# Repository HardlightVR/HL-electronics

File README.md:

# Hardlight Electronics

Contains the PCBA designs used in the Hardlight suit, designed in Eagle™. 

### Organization
- **MKIIIA** contains older versions of the Hardlight electronics, used in the experimental run of 25. Also includes incomplete designs for a the HL Bluetooth module. 
- **MKIIIB** contains the final designs used in the 100 and 500 run HL releases, as well as the completed WiFi module. 

### Please note:
Hardlight VR was a complex project involving many dependencies. We have decided to open the code in the hopes that others may make use of the tools and plugins we built over the years. However, some software may not have been built or tested in some time, and may require changes to be used with the latest VR software and technology. 

### Contributing and Contact
We welcome any and all interest in derivative projects made from this software, edits to the software, and updates to the plugins and drivers! If you are interested in contributing to the public Hardlight repositories, please create an issue, or email hardlightvr@gmail.com.

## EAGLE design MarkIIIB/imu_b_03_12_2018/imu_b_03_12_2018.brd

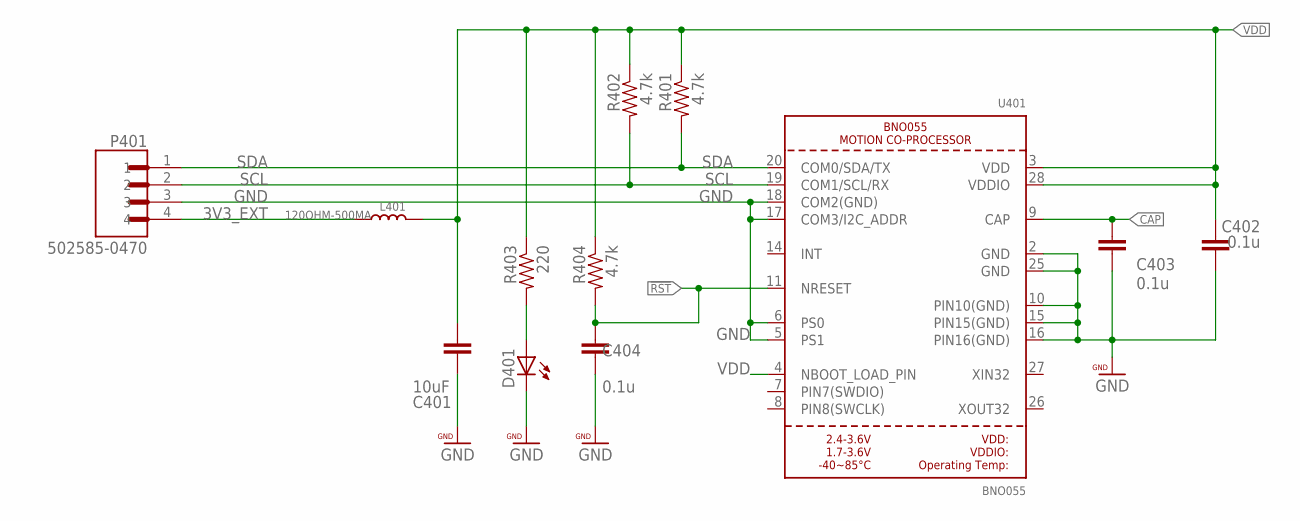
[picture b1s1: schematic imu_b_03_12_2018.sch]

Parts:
C401: 10uF; 0402-CAP
C402, C403, C404: 0.1u; 0402-CAP
D401: LEDCHIP-LED0603; CHIP-LED0603
L401: 120OHM-500MA; L0603
P401: 502585-0470; MOLEX_502585-0470
R401, R402, R404: 4.7k; EIA-0402
R403: 220; EIA-0402
U401: BNO055

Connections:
3V3_EXT: L401.2, P401.4
!RST: C404.1, R404.2, U401.11 (NRESET)
CAP: C403.1, U401.9 (CAP)
GND: C401.2, C402.2, C403.2, C404.2, D401.C, P401.3, U401.2 (GND), U401.5 (PS1), U401.6 (PS0), U401.10 (PIN10(GND)), U401.15 (PIN15(GND)), U401.16 (PIN16(GND)), U401.17 (COM3/I2C_ADDR), U401.18 (COM2(GND)), U401.25 (GND)
unnamed: D401.A, R403.2
SCL: P401.2, R402.2, U401.19 (COM1/SCL/RX)
SDA: P401.1, R401.2, U401.20 (COM0/SDA/TX)
VDD: C401.1, C402.1, L401.1, R401.1, R402.1, R403.1, R404.1, U401.3 (VDD), U401.4 (NBOOT_LOAD_PIN), U401.28 (VDDIO)

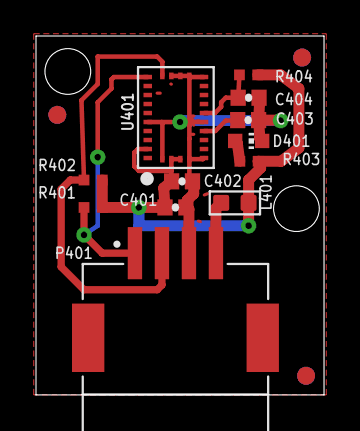
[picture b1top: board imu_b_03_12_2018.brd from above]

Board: 2 copper layers, 16.0 x 19.9 mm, 15 parts (0 on the bottom side), 8 nets.

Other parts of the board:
$$U$2: CIRCLE-1MM-2R
U$1, U$3: CIRCLE-1MM-2R

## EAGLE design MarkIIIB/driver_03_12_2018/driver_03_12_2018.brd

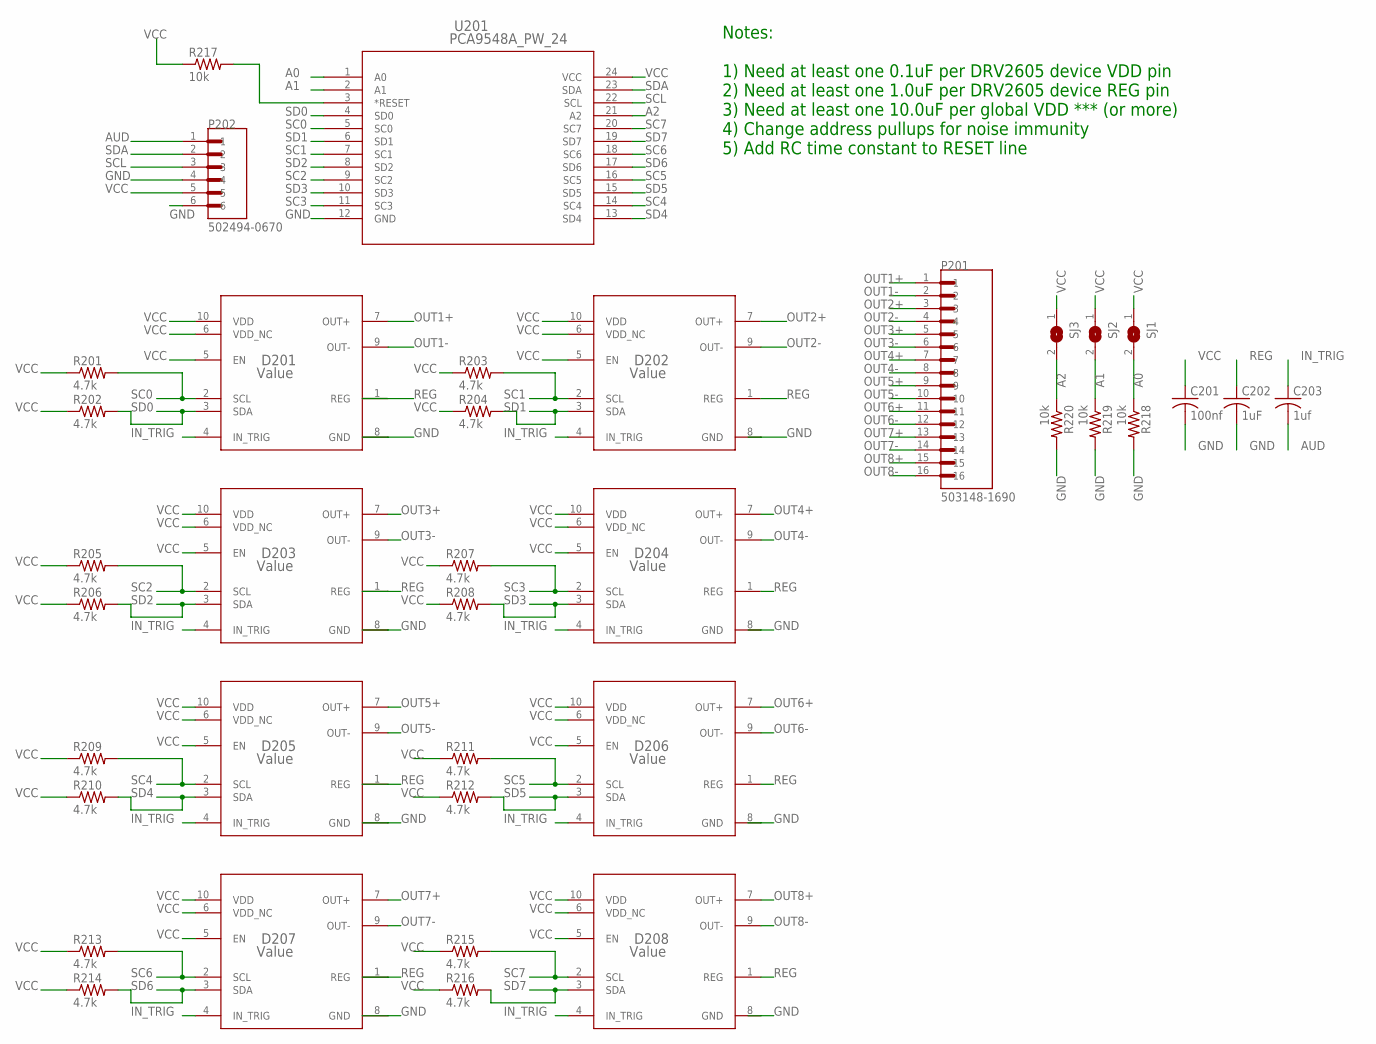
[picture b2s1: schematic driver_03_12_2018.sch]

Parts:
C201: 100nf; C0603
C202: 1uF; C0603
C203: 1uf; C0603
D201, D202, D203, D204, D205, D206, D207, D208: Value; DGS0010A
P201: 503148-1690; MOLEX_503148-1690
P202: 502494-0670; MOLEX_502494-0670
R201, R202, R203, R204, R205, R206, R207, R208, R209, R210, R211, R212, R213, R214, R215, R216: 4.7k; EIA-0402
R217: 10k; R0402
R218, R219, R220: 10k; EIA-0402
SJ1, SJ2, SJ3: SJ
U201: PCA9548A_PW_24; PW24

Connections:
A0: R218.1, SJ1.2, U201.1 (A0)
A1: R219.1, SJ2.2, U201.2 (A1)
A2: R220.1, SJ3.2, U201.21 (A2)
AUD: C203.2, P202.1
GND: C201.2, C202.2, D201.8 (GND), D202.8 (GND), D203.8 (GND), D204.8 (GND), D205.8 (GND), D206.8 (GND), D207.8 (GND), D208.8 (GND), P202.4, P202.6, R218.2, R219.2, R220.2, U201.12 (GND)
IN_TRIG: C203.1, D201.4 (IN_TRIG), D202.4 (IN_TRIG), D203.4 (IN_TRIG), D204.4 (IN_TRIG), D205.4 (IN_TRIG), D206.4 (IN_TRIG), D207.4 (IN_TRIG), D208.4 (IN_TRIG)
OUT1+: D201.7 (OUT+), P201.1
OUT1-: D201.9 (OUT-), P201.2
OUT2+: D202.7 (OUT+), P201.3
OUT2-: D202.9 (OUT-), P201.4
OUT3+: D203.7 (OUT+), P201.5
OUT3-: D203.9 (OUT-), P201.6
OUT4+: D204.7 (OUT+), P201.7
OUT4-: D204.9 (OUT-), P201.8
OUT5+: D205.7 (OUT+), P201.9
OUT5-: D205.9 (OUT-), P201.10
OUT6+: D206.7 (OUT+), P201.11
OUT6-: D206.9 (OUT-), P201.12
OUT7+: D207.7 (OUT+), P201.13
OUT7-: D207.9 (OUT-), P201.14
OUT8+: D208.7 (OUT+), P201.15
OUT8-: D208.9 (OUT-), P201.16
REG: C202.1, D201.1 (REG), D202.1 (REG), D203.1 (REG), D204.1 (REG), D205.1 (REG), D206.1 (REG), D207.1 (REG), D208.1 (REG)
RESET: R217.2, U201.3 (*RESET)
SC0: D201.2 (SCL), R201.2, U201.5 (SC0)
SC1: D202.2 (SCL), R203.2, U201.7 (SC1)
SC2: D203.2 (SCL), R205.2, U201.9 (SC2)
SC3: D204.2 (SCL), R207.2, U201.11 (SC3)
SC4: D205.2 (SCL), R209.2, U201.14 (SC4)
SC5: D206.2 (SCL), R211.2, U201.16 (SC5)
SC6: D207.2 (SCL), R213.2, U201.18 (SC6)
SC7: D208.2 (SCL), R215.2, U201.20 (SC7)
SCL: P202.3, U201.22 (SCL)
SD0: D201.3 (SDA), R202.2, U201.4 (SD0)
SD1: D202.3 (SDA), R204.2, U201.6 (SD1)
SD2: D203.3 (SDA), R206.2, U201.8 (SD2)
SD3: D204.3 (SDA), R208.2, U201.10 (SD3)
SD4: D205.3 (SDA), R210.2, U201.13 (SD4)
SD5: D206.3 (SDA), R212.2, U201.15 (SD5)
SD6: D207.3 (SDA), R214.2, U201.17 (SD6)
SD7: D208.3 (SDA), R216.2, U201.19 (SD7)
SDA: P202.2, U201.23 (SDA)
VCC: C201.1, D201.5 (EN), D201.6 (VDD_NC), D201.10 (VDD), D202.5 (EN), D202.6 (VDD_NC), D202.10 (VDD), D203.5 (EN), D203.6 (VDD_NC), D203.10 (VDD), D204.5 (EN), D204.6 (VDD_NC), D204.10 (VDD), D205.5 (EN), D205.6 (VDD_NC), D205.10 (VDD), D206.5 (EN), D206.6 (VDD_NC), D206.10 (VDD), D207.5 (EN), D207.6 (VDD_NC), D207.10 (VDD), D208.5 (EN), D208.6 (VDD_NC), D208.10 (VDD), P202.5, R201.1, R202.1, R203.1, R204.1, R205.1, R206.1, R207.1, R208.1, R209.1, R210.1, R211.1, R212.1, R213.1, R214.1, R215.1, R216.1, R217.1, SJ1.1, SJ2.1, SJ3.1, U201.24 (VCC)

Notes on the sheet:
Notes: 1) Need at least one 0.1uF per DRV2605 device VDD pin 2) Need at least one 1.0uF per DRV2605 device REG pin 3) Need at least one 10.0uF per global VDD *** (or more) 4) Change address pullups for noise immunity 5) Add RC time constant to RESET line

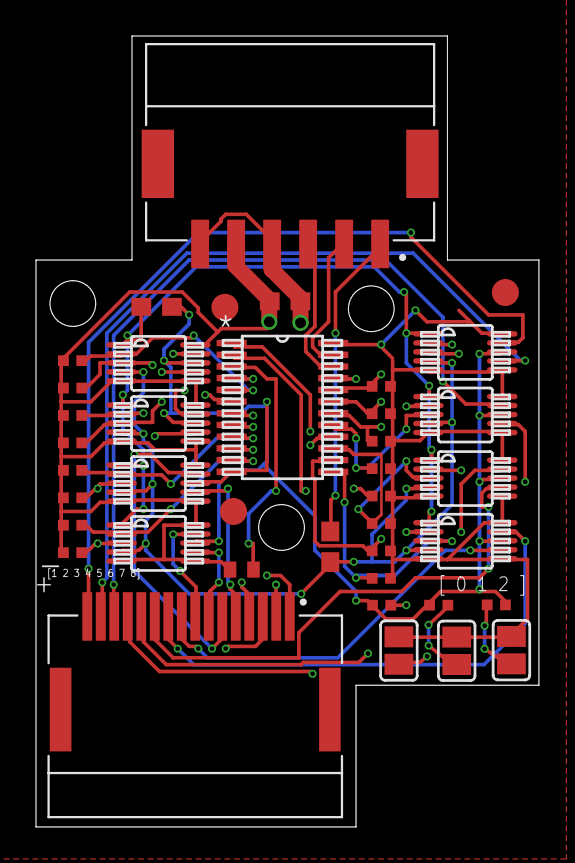
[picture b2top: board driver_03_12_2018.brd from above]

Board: 4 copper layers, 27.9 x 43.9 mm, 40 parts (0 on the bottom side), 43 nets.

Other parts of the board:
U$1, U$2, U$4: FIDUCIAL_G15

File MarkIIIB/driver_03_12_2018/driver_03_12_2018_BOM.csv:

Qty,Value,Device,Package,Parts,Description
3,,SJ,SJ,"SJ1, SJ2, SJ3",SMD solder JUMPER
1,100nf,C-USC0603,C0603,C201,"CAPACITOR, American symbol"
4,10k,R-US_R0402,R0402,"R219, R217, R218, R220","RESISTOR, American symbol"
1,1uF,C-USC0603,C0603,C202,"CAPACITOR, American symbol"
1,1uf,C-USC0603,C0603,C203,"CAPACITOR, American symbol"
16,4.7k,R-US_R0402,R0402,"R201, R202, R203, R204, R205, R206, R207, R208, R209, R210, R211, R212, R213, R214, R215, R216","RESISTOR, American symbol"
1,502494-0670,502494-0670,MOLEX_502494-0670,P202,"2.00mm Pitch CLIK-Mate Wire-to-Board PCB Receptacle, Single Row, Right Angle, 6 Circuits"
1,503148-1690,503148-1690,MOLEX_503148-1690,P201,"1.50mm Pitch CLIK-Mate Wire-to-Board PCB Receptacle, Dual Row, Right Angle, 16 Circuits"
1,PCA9548A_PW_24,PCA9548A_PW_24,PW24,U201,
8,Value,DRV2605LDGSR,DGS0010A,"D201, D202, D203, D204, D205, D206, D207, D208",

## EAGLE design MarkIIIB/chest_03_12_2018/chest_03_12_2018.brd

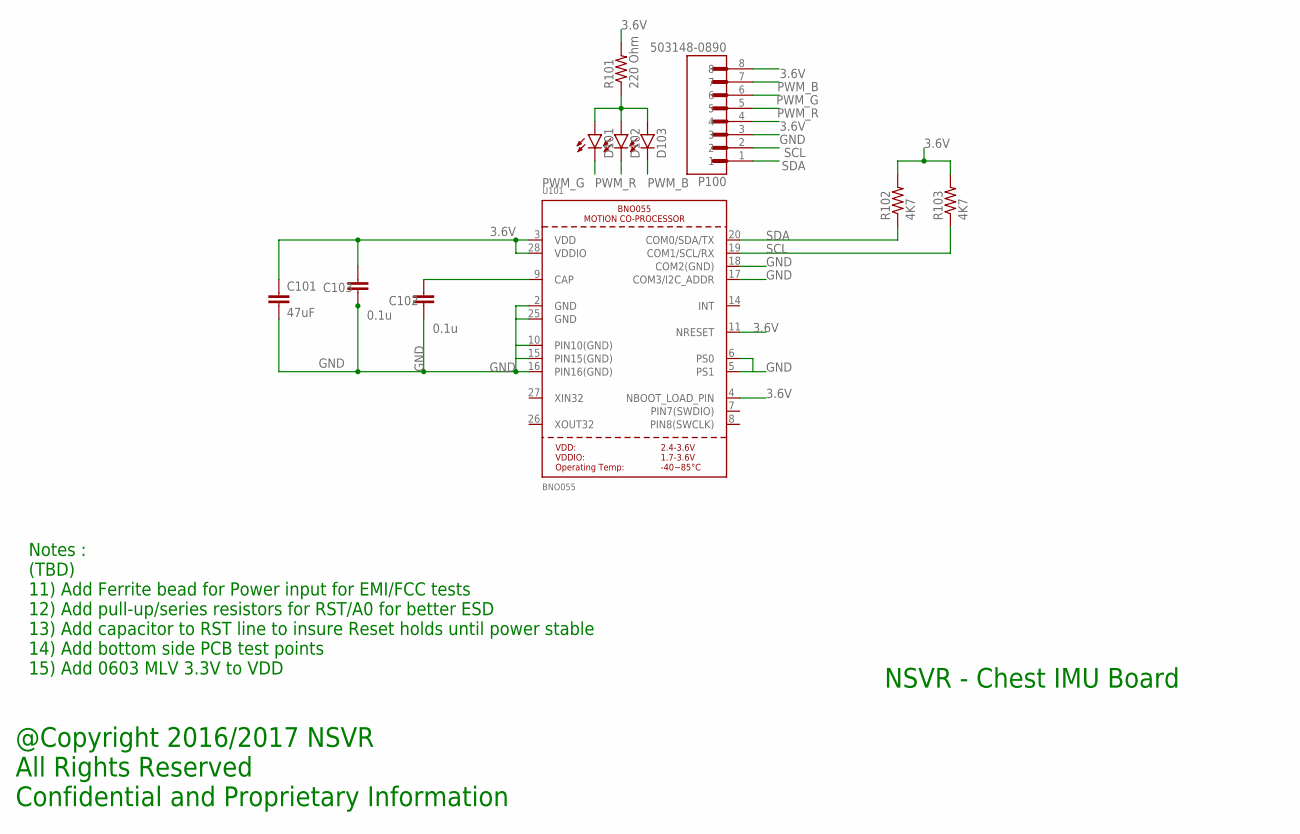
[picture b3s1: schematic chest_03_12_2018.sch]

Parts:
C101: 47uF; 1206
C102, C103: 0.1u; 0402-CAP
D101, D102, D103: LED0603; LED-0603
P100: 503148-0890; MOLEX_503148-0890
R101: 220 Ohm; EIA-0402
R102, R103: 4K7; EIA-0402
U101: BNO055

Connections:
3.6V: C101.1, C103.1, P100.4, P100.8, R101.2, R102.2, R103.2, U101.3 (VDD), U101.4 (NBOOT_LOAD_PIN), U101.11 (NRESET), U101.28 (VDDIO)
BYPASS: C102.1, U101.9 (CAP)
GND: C101.2, C102.2, C103.2, P100.3, U101.2 (GND), U101.5 (PS1), U101.6 (PS0), U101.10 (PIN10(GND)), U101.15 (PIN15(GND)), U101.16 (PIN16(GND)), U101.17 (COM3/I2C_ADDR), U101.18 (COM2(GND)), U101.25 (GND)
unnamed: D101.A, D102.A, D103.A, R101.1
PWM_B: D103.C, P100.7
PWM_G: D101.C, P100.6
PWM_R: D102.C, P100.5
SCL: P100.2, R103.1, U101.19 (COM1/SCL/RX)
SDA: P100.1, R102.1, U101.20 (COM0/SDA/TX)

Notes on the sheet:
NSVR - Chest IMU Board
@Copyright 2016/2017 NSVR All Rights Reserved Confidential and Proprietary Information
Notes : (TBD) 11) Add Ferrite bead for Power input for EMI/FCC tests 12) Add pull-up/series resistors for RST/A0 for better ESD 13) Add capacitor to RST line to insure Reset holds until power stable 14) Add bottom side PCB test points 15) Add 0603 MLV 3.3V to VDD

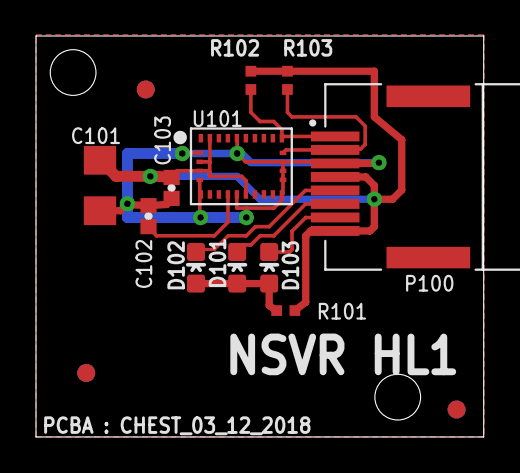
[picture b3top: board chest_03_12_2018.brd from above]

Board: 2 copper layers, 24.9 x 22.3 mm, 15 parts (1 on the bottom side), 9 nets.

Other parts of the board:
U$1, U$3, U$4: CIRCLE-1MM-3R
U$2: NSVR_LOGO

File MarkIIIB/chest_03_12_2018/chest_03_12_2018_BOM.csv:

"Qty";"Value";"Device";"Package";"Parts";"Description";"";
"3";"";"LED0603";"LED-0603";"D101, D102, D103";"LEDs";"";
"2";"0.1u";"C-USC0402";"C0402";"C102, C103";"CAPACITOR, American symbol";"";
"1";"220 Ohm";"R-US_R0402";"R0402";"R101";"RESISTOR, American symbol";"";
"1";"47uF";"CAP1206";"1206";"C101";"Capacitor";"";
"2";"4K7";"R-US_R0402";"R0402";"R102, R103";"RESISTOR, American symbol";"";
"1";"503148-0890";"503148-0890";"MOLEX_503148-0890";"P100";"1.5wb Dual r/a Embs Tape Pkg 8p";"";
"1";"BNO055";"BNO055";"BNO055";"U101";"BNO055 - Motion Co-Processor";"";

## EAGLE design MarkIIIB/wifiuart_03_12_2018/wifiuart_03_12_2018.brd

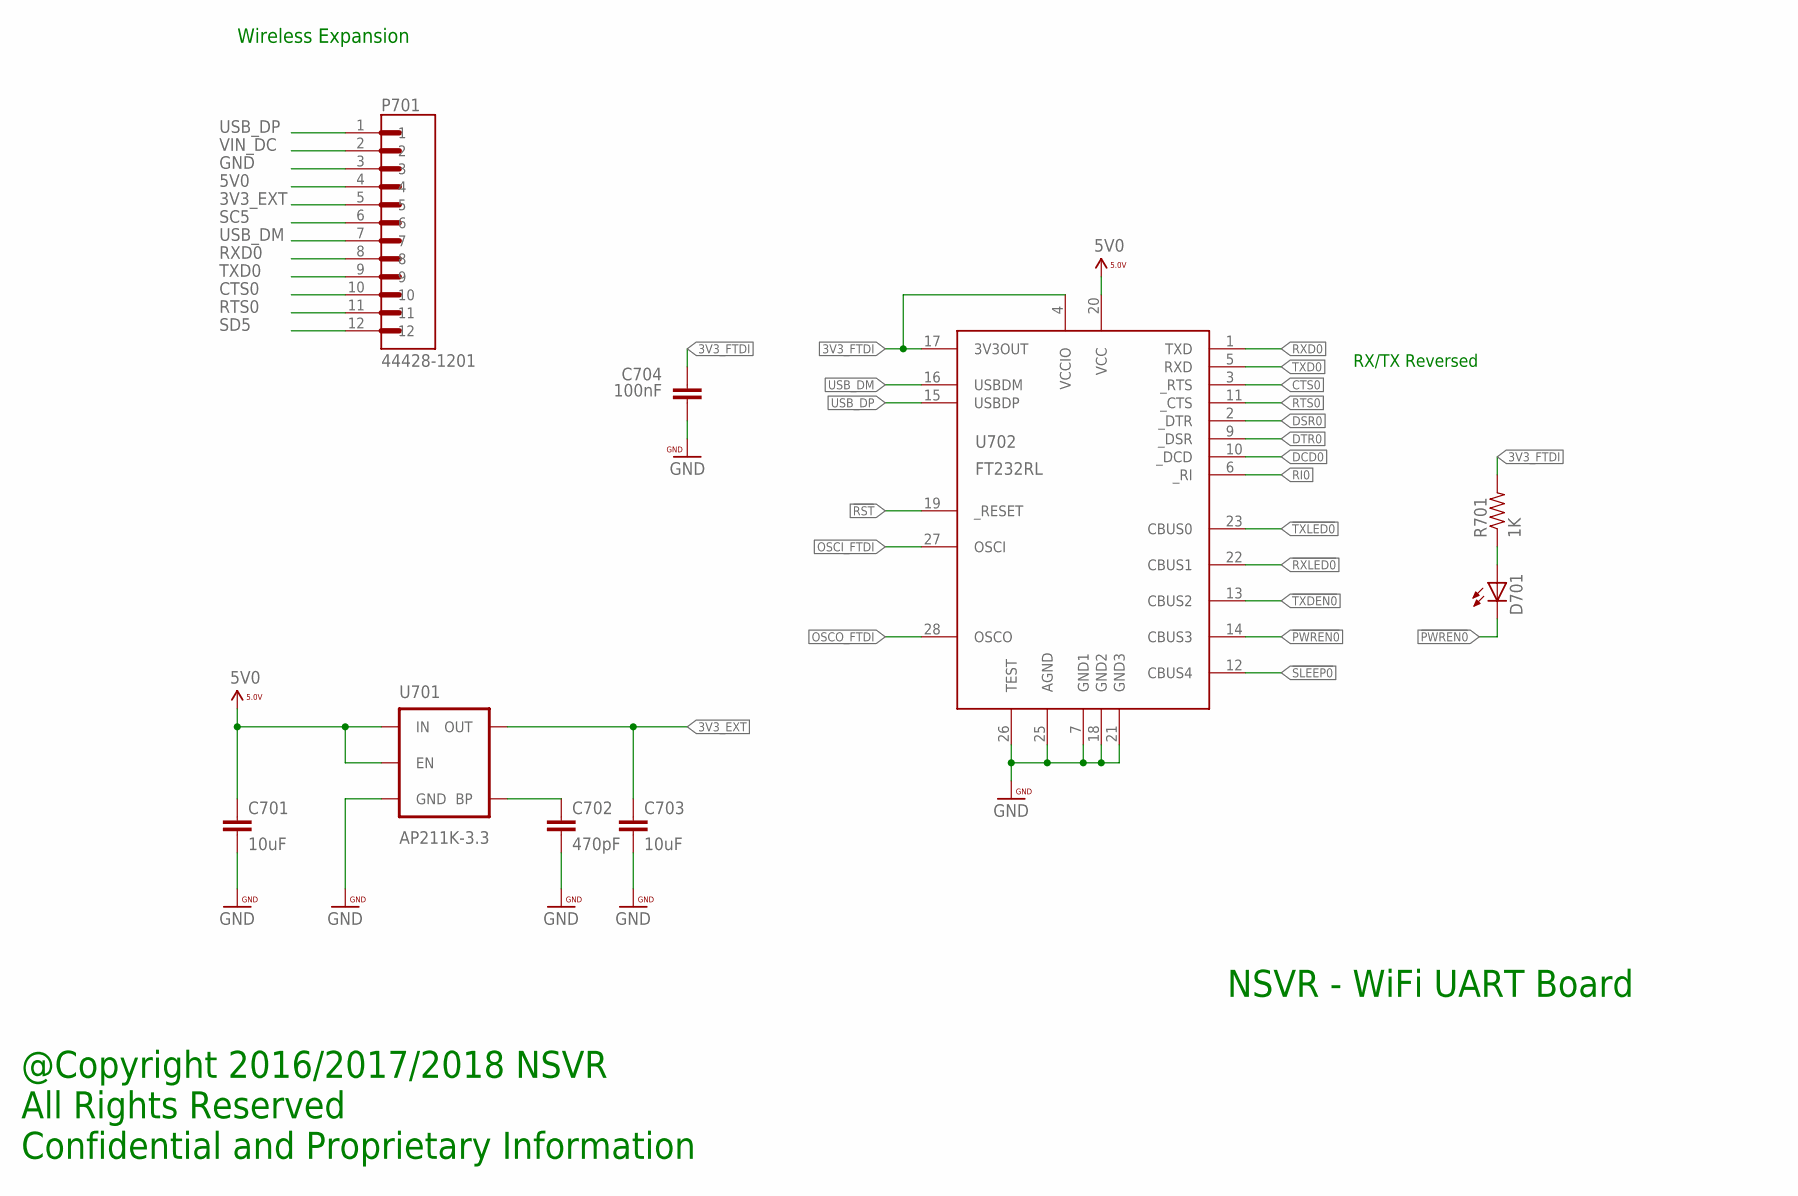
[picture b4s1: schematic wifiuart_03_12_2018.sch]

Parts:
C701, C703: 10uF; 0603-CAP
C702: 470pF; 0402-CAP
C704: 100nF; 0402-CAP
D701: LEDCHIP-LED0603; CHIP-LED0603
P701: 44428-1201; MOLEX_44428-1201
R701: 1K; EIA-0402
U701: AP211K-3.3; SOT23-5
U702: FT232RL; SSOP28DB

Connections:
3V3_EXT: C703.1, P701.5, U701.5 (OUT)
3V3_FTDI: C704.1, R701.2, U702.4 (VCCIO), U702.17 (3V3OUT)
5V0: C701.1, P701.4, U701.1 (IN), U701.3 (EN), U702.20 (VCC)
!PWREN0: D701.C, U702.14 (CBUS3)
!RST: U702.19 (_RESET)
!RXLED0: U702.22 (CBUS1)
!SLEEP0: U702.12 (CBUS4)
!TXDEN0: U702.13 (CBUS2)
!TXLED0: U702.23 (CBUS0)
CTS0: P701.10, U702.3 (_RTS)
DCD0: U702.10 (_DCD)
DSR0: U702.2 (_DTR)
DTR0: U702.9 (_DSR)
GND: C701.2, C702.2, C703.2, C704.2, P701.3, U701.2 (GND), U702.7 (GND1), U702.18 (GND2), U702.21 (GND3), U702.25 (AGND), U702.26 (TEST)
unnamed: D701.A, R701.1
unnamed: C702.1, U701.4 (BP)
OSCI_FTDI: U702.27 (OSCI)
OSCO_FTDI: U702.28 (OSCO)
RI0: U702.6 (_RI)
RTS0: P701.11, U702.11 (_CTS)
RXD0: P701.8, U702.1 (TXD)
SC5: P701.6
SD5: P701.12
TXD0: P701.9, U702.5 (RXD)
USB_DM: P701.7, U702.16 (USBDM)
USB_DP: P701.1, U702.15 (USBDP)
VIN_DC: P701.2

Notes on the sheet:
@Copyright 2016/2017/2018 NSVR All Rights Reserved Confidential and Proprietary Information
NSVR - WiFi UART Board
Wireless Expansion
RX/TX Reversed

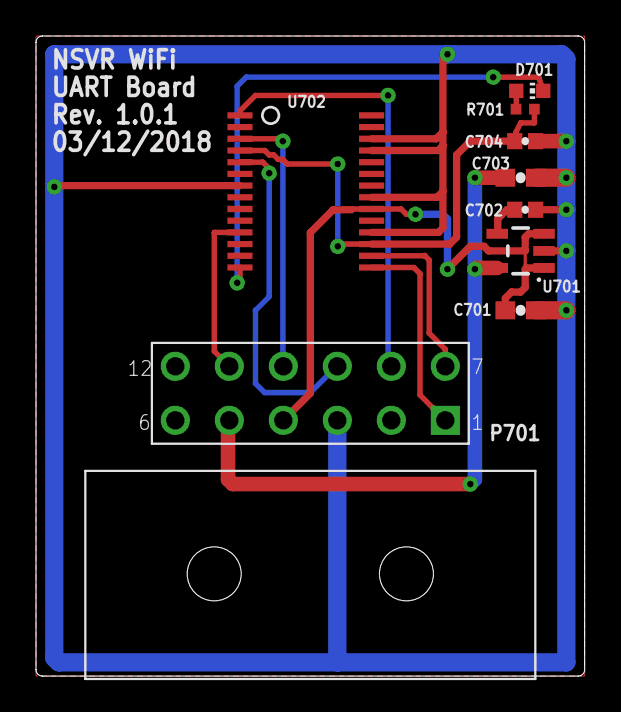
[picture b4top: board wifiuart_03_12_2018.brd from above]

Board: 2 copper layers, 30.5 x 35.6 mm, 9 parts (0 on the bottom side), 13 nets.

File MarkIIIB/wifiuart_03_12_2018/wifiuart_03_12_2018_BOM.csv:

"Qty";"Value";"Device";"Package";"Parts";"Description";"";
"1";"";"LEDCHIP-LED0603";"CHIP-LED0603";"D701";"LED";"";
"1";"100nF";"CAP0402-CAP";"0402-CAP";"C704";"Capacitor";"";
"2";"10uF";"CAP0603-CAP";"0603-CAP";"C701, C703";"Capacitor";"";
"1";"1K";"RESISTOR0402-TYP";"EIA-0402";"R701";"Resistor";"";
"1";"44428-1201";"44428-1201";"MOLEX_44428-1201";"P701";"Conn Wire to Board HDR 12 POS 3mm Solder RA Thru-Hole Micro-Fit 3.0 BMI? Tray";"";
"1";"470pF";"CAP0402-CAP";"0402-CAP";"C702";"Capacitor";"";
"1";"AP211K-3.3";"V_REG_MIC52053.3V";"SOT23-5";"U701";"V_REG MIC5205 Standard 3.3V, 5V, and Adjustable 150mA LDO voltage regulator in SOT-23 layout. Micrel part MIC5205. BP (by-pass) pin is used to lower output noise with 470pF cap, may be left open. On the adjustable version BP is used to set output.";"";
"1";"FT232RL";"FT232RL";"SSOP28DB";"U702";"USB UART";"";

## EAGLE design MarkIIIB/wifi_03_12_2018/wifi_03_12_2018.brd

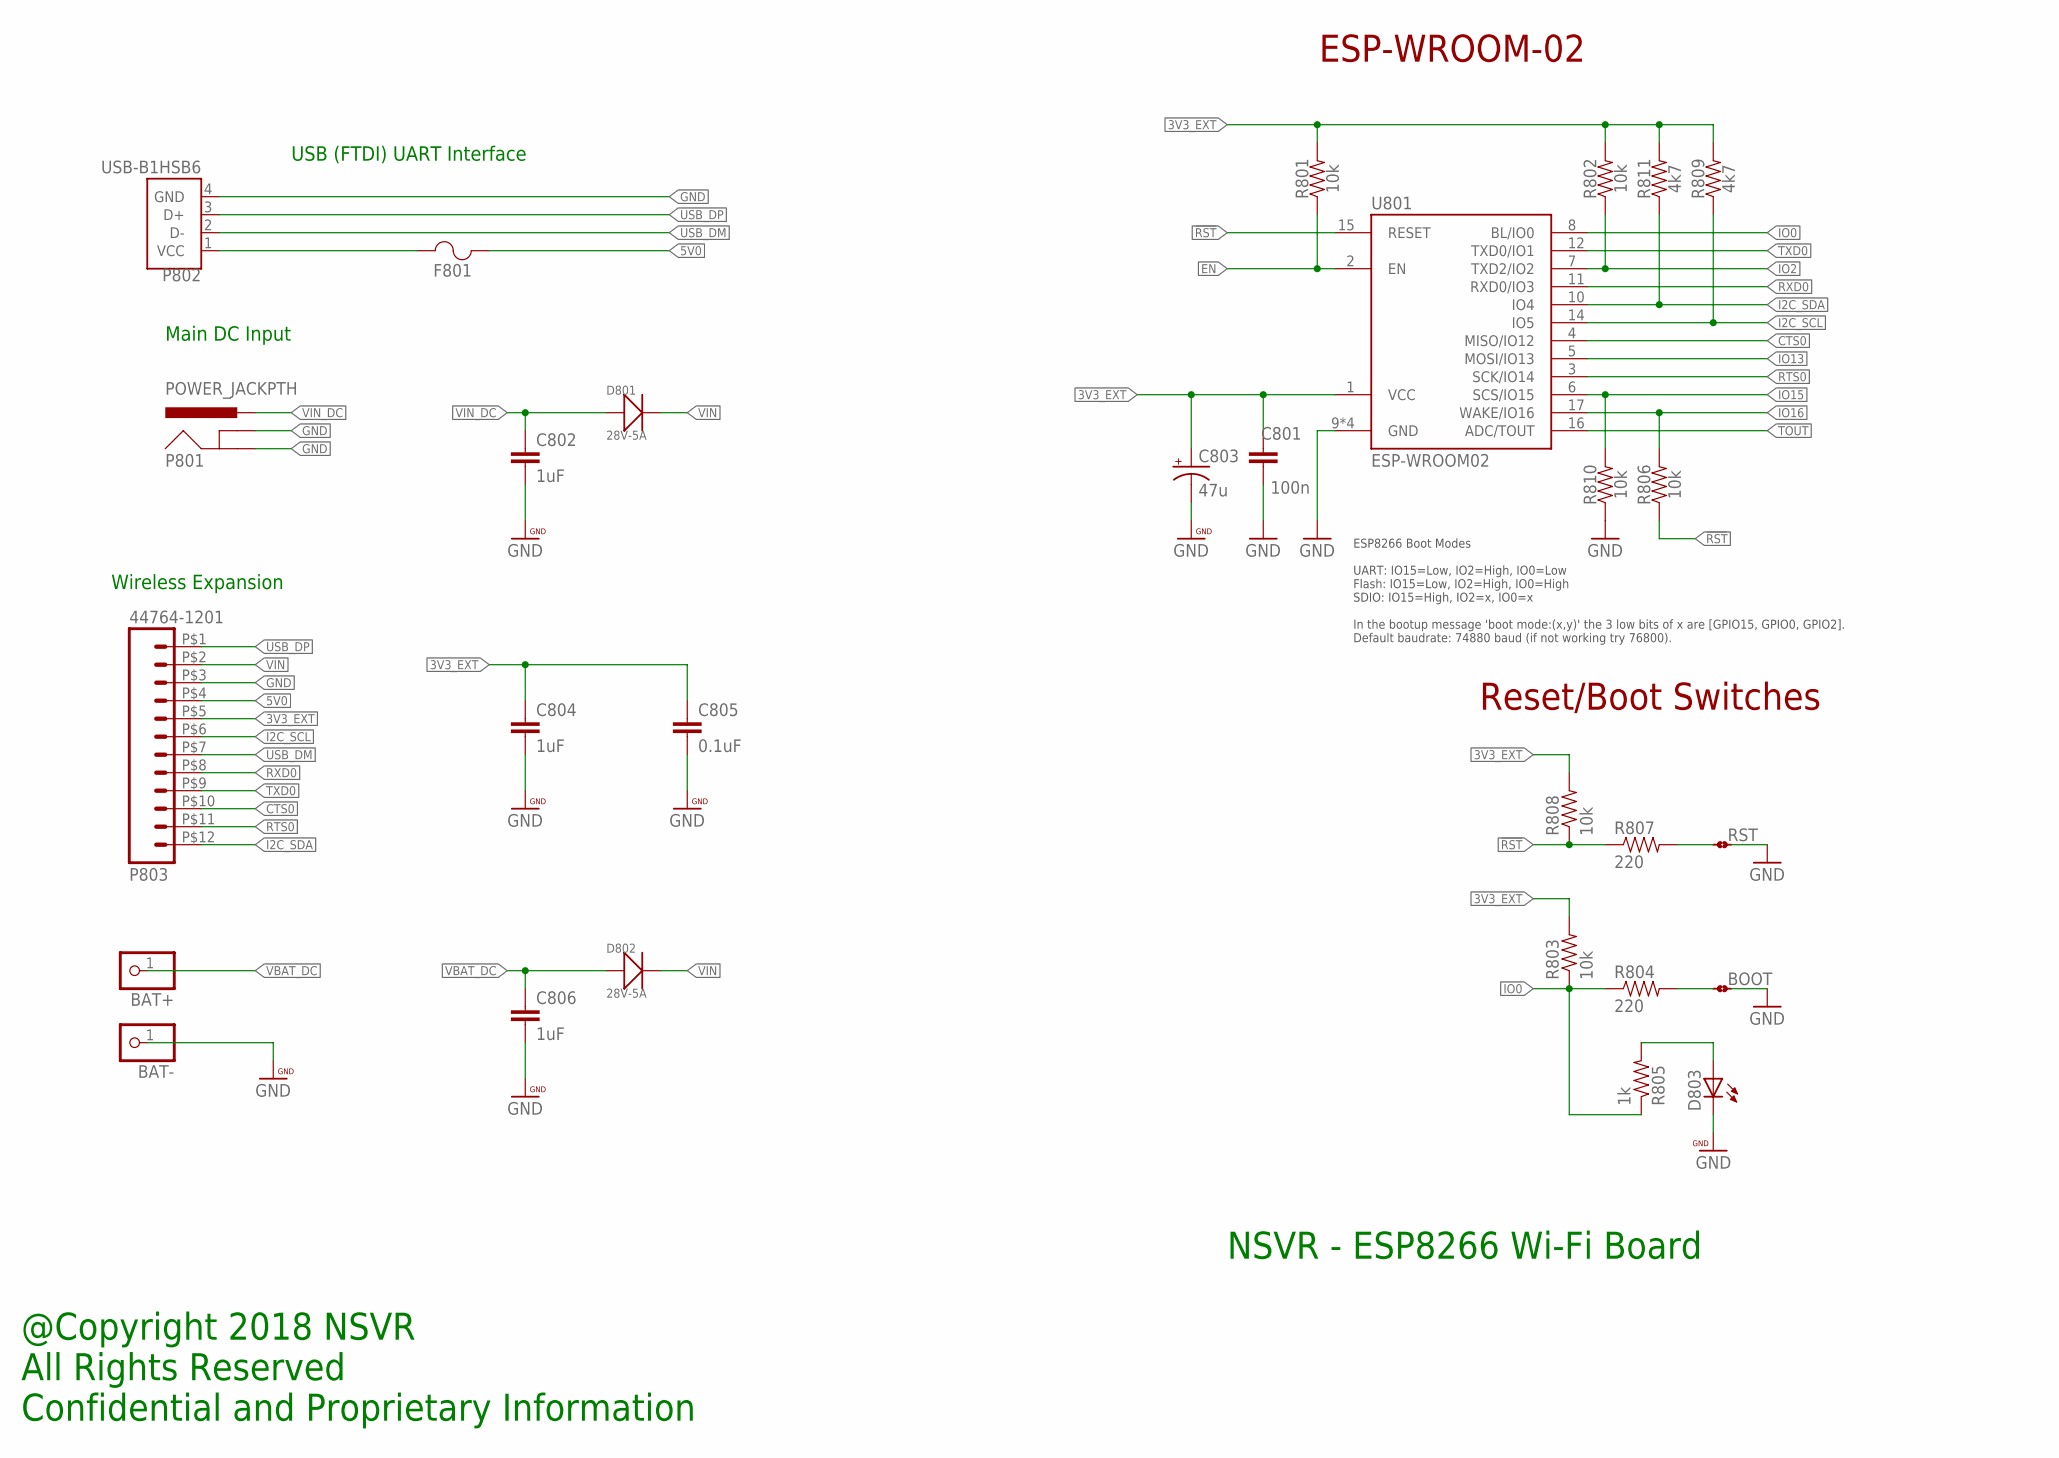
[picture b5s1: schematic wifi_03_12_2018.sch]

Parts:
BAT+: WPAD-1-PTH; WPAD-1-PTH-2.54
BAT-: WPAD-1-PTH; WPAD-1-PTH-2.54
BOOT: JMP-2-NO-PTH; JMP-2-NO-PTH-2.54
C801: 100n; 0402-CAP
C802, C804, C806: 1uF; 0402-CAP
C803: 47u; PANASONIC_D
C805: 0.1uF; 0402-CAP
D801, D802: 28V-5A; DO-214AA
D803: LEDCHIP-LED0603; CHIP-LED0603
F801: 1206L050YR; 1206LSERIES
P801: POWER_JACKPTH; POWER_JACK_PTH
P802: USB-B1HSB6; OST_USB-B1HSB6
P803: 44764-1201
R801, R802, R803, R806, R808, R810: 10k; EIA-0402
R804, R807: 220; EIA-0402
R805: 1k; EIA-0402
R809, R811: 4k7; EIA-0402
RST: JMP-2-NO-PTH; JMP-2-NO-PTH-2.54
U801: ESP-WROOM02

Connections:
3V3_EXT: C801.2, C803.+, C804.1, C805.1, P803.P$5 (5), R801.2, R802.2, R803.2, R808.2, R809.2, R811.2, U801.1 (VCC)
5V0: F801.2, P803.P$4 (4)
!RST: R806.1, R807.1, R808.1, U801.15 (RESET)
CTS0: P803.P$10 (10), U801.4 (MISO/IO12)
EN: R801.1, U801.2 (EN)
GND: BAT-.1, BOOT.2, C801.1, C802.2, C803.-, C804.2, C805.2, C806.2, D803.C, P801.GND, P801.GNDBREAK, P802.4 (GND), P803.P$3 (3), R810.1, RST.2, U801.9 (GND), U801.13 (GND), U801.18 (GND), U801.TP (GND)
I2C_SCL: P803.P$6 (6), R809.1, U801.14 (IO5)
I2C_SDA: P803.P$12 (12), R811.1, U801.10 (IO4)
IO0: R803.1, R804.1, R805.1, U801.8 (BL/IO0)
IO2: R802.1, U801.7 (TXD2/IO2)
IO13: U801.5 (MOSI/IO13)
IO15: R810.2, U801.6 (SCS/IO15)
IO16: R806.2, U801.17 (WAKE/IO16)
LED1: D803.A, R805.2
unnamed: R807.2, RST.1
unnamed: BOOT.1, R804.2
RTS0: P803.P$11 (11), U801.3 (SCK/IO14)
RXD0: P803.P$8 (8), U801.11 (RXD0/IO3)
TOUT: U801.16 (ADC/TOUT)
TXD0: P803.P$9 (9), U801.12 (TXD0/IO1)
USB_DM: P802.2 (D-), P803.P$7 (7)
USB_DP: P802.3 (D+), P803.P$1 (1)
VBAT_DC: BAT+.1, C806.1, D802.+
VBUS_IN: F801.1, P802.1 (VCC)
VIN: D801.-, D802.-, P803.P$2 (2)
VIN_DC: C802.1, D801.+, P801.PWR

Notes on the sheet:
Wireless Expansion
Main DC Input
USB (FTDI) UART Interface
@Copyright 2018 NSVR All Rights Reserved Confidential and Proprietary Information
NSVR - ESP8266 Wi-Fi Board
ESP-WROOM-02
ESP8266 Boot Modes UART: IO15=Low, IO2=High, IO0=Low Flash: IO15=Low, IO2=High, IO0=High SDIO: IO15=High, IO2=x, IO0=x In the bootup message 'boot mode:(x,y)' the 3 low bits of x are [GPIO15, GPIO0, GPIO2]. Default baudrate: 74880 baud (if not working try 76800).
Reset/Boot Switches

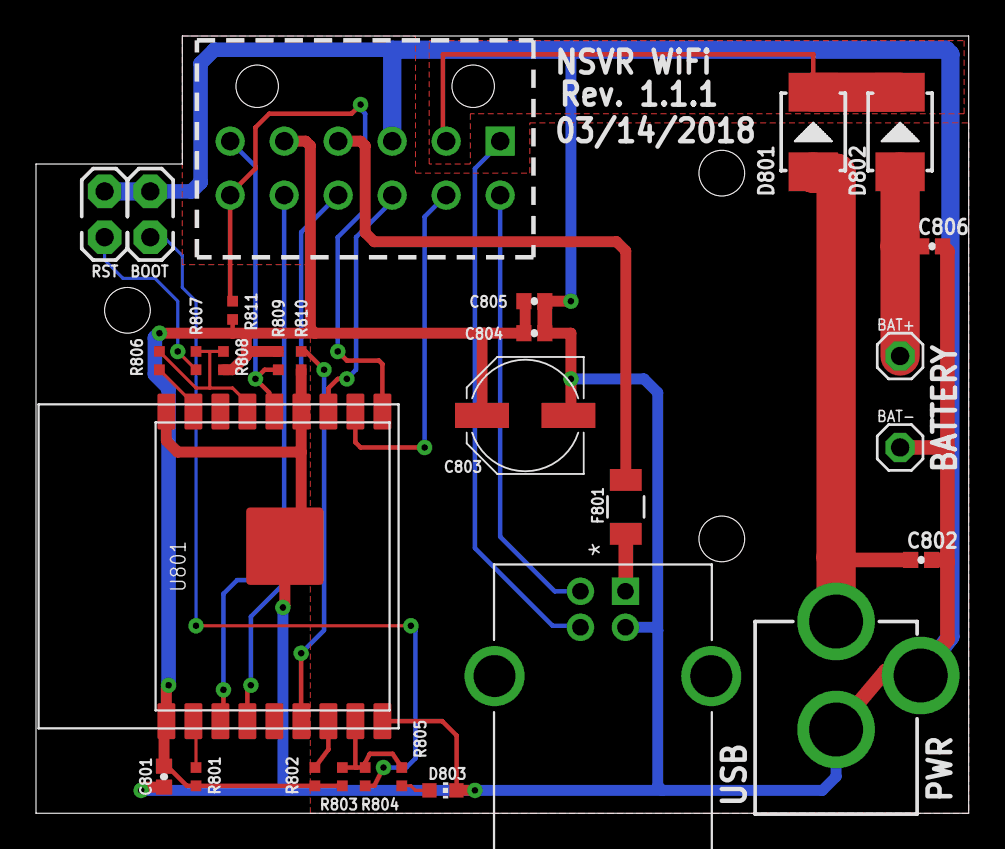
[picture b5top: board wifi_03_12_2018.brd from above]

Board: 2 copper layers, 51.8 x 43.2 mm, 29 parts (0 on the bottom side), 24 nets.

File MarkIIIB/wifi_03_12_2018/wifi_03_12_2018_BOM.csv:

"Qty";"Value";"Device";"Package";"Parts";"Description";"";
"2";"";"JMP-2-NO-PTH";"JMP-2-NO-PTH-2.54";"BOOT, RST";"Two Terminal Jumper - Normally Open";"";
"1";"";"LEDCHIP-LED0603";"CHIP-LED0603";"D803";"LED";"";
"2";"";"WPAD-1-PTH";"WPAD-1-PTH-2.54";"BAT+, BAT-";"Wire Pad - Single";"";
"1";"0.1uF";"CAP0402-CAP";"0402-CAP";"C805";"Capacitor";"";
"1";"100n";"CAP0402-CAP";"0402-CAP";"C801";"Capacitor";"";
"6";"10k";"RESISTOR0402-TYP";"EIA-0402";"R801, R802, R803, R806, R808, R810";"Resistor";"";
"1";"1206L050YR";"1206L050YR";"1206LSERIES";"F801";"";"";
"1";"1k";"RESISTOR0402-TYP";"EIA-0402";"R805";"Resistor";"";
"3";"1uF";"CAP0402-CAP";"0402-CAP";"C802, C804, C806";"Capacitor";"";
"2";"220";"RESISTOR0402-TYP";"EIA-0402";"R804, R807";"Resistor";"";
"2";"28V-5A";"SMD-DIODE-SCHOTTKY-28V-5A(DO-214AA)";"DO-214AA";"D801, D802";"304020021";"";
"1";"44764-1201";"44764-1201";"44764-1201";"P803";"";"";
"1";"47u";"CAP_POLD";"PANASONIC_D";"C803";"Capacitor Polarized";"";
"2";"4k7";"RESISTOR0402-TYP";"EIA-0402";"R809, R811";"Resistor";"";
"1";"ESP-WROOM02";"ESP-WROOM02";"ESP-WROOM02";"U801";"Espressif ESP-WROOM-02  and AI-Thinker ESP-12 ESP8266 WiFi/WLAN Module";"";
"1";"POWER_JACKPTH";"POWER_JACKPTH";"POWER_JACK_PTH";"P801";"Power Jack";"";
"1";"USB-B1HSB6";"USB-B1HSB6";"OST_USB-B1HSB6";"P802";"Conn Usb Type b r/a Black";"";

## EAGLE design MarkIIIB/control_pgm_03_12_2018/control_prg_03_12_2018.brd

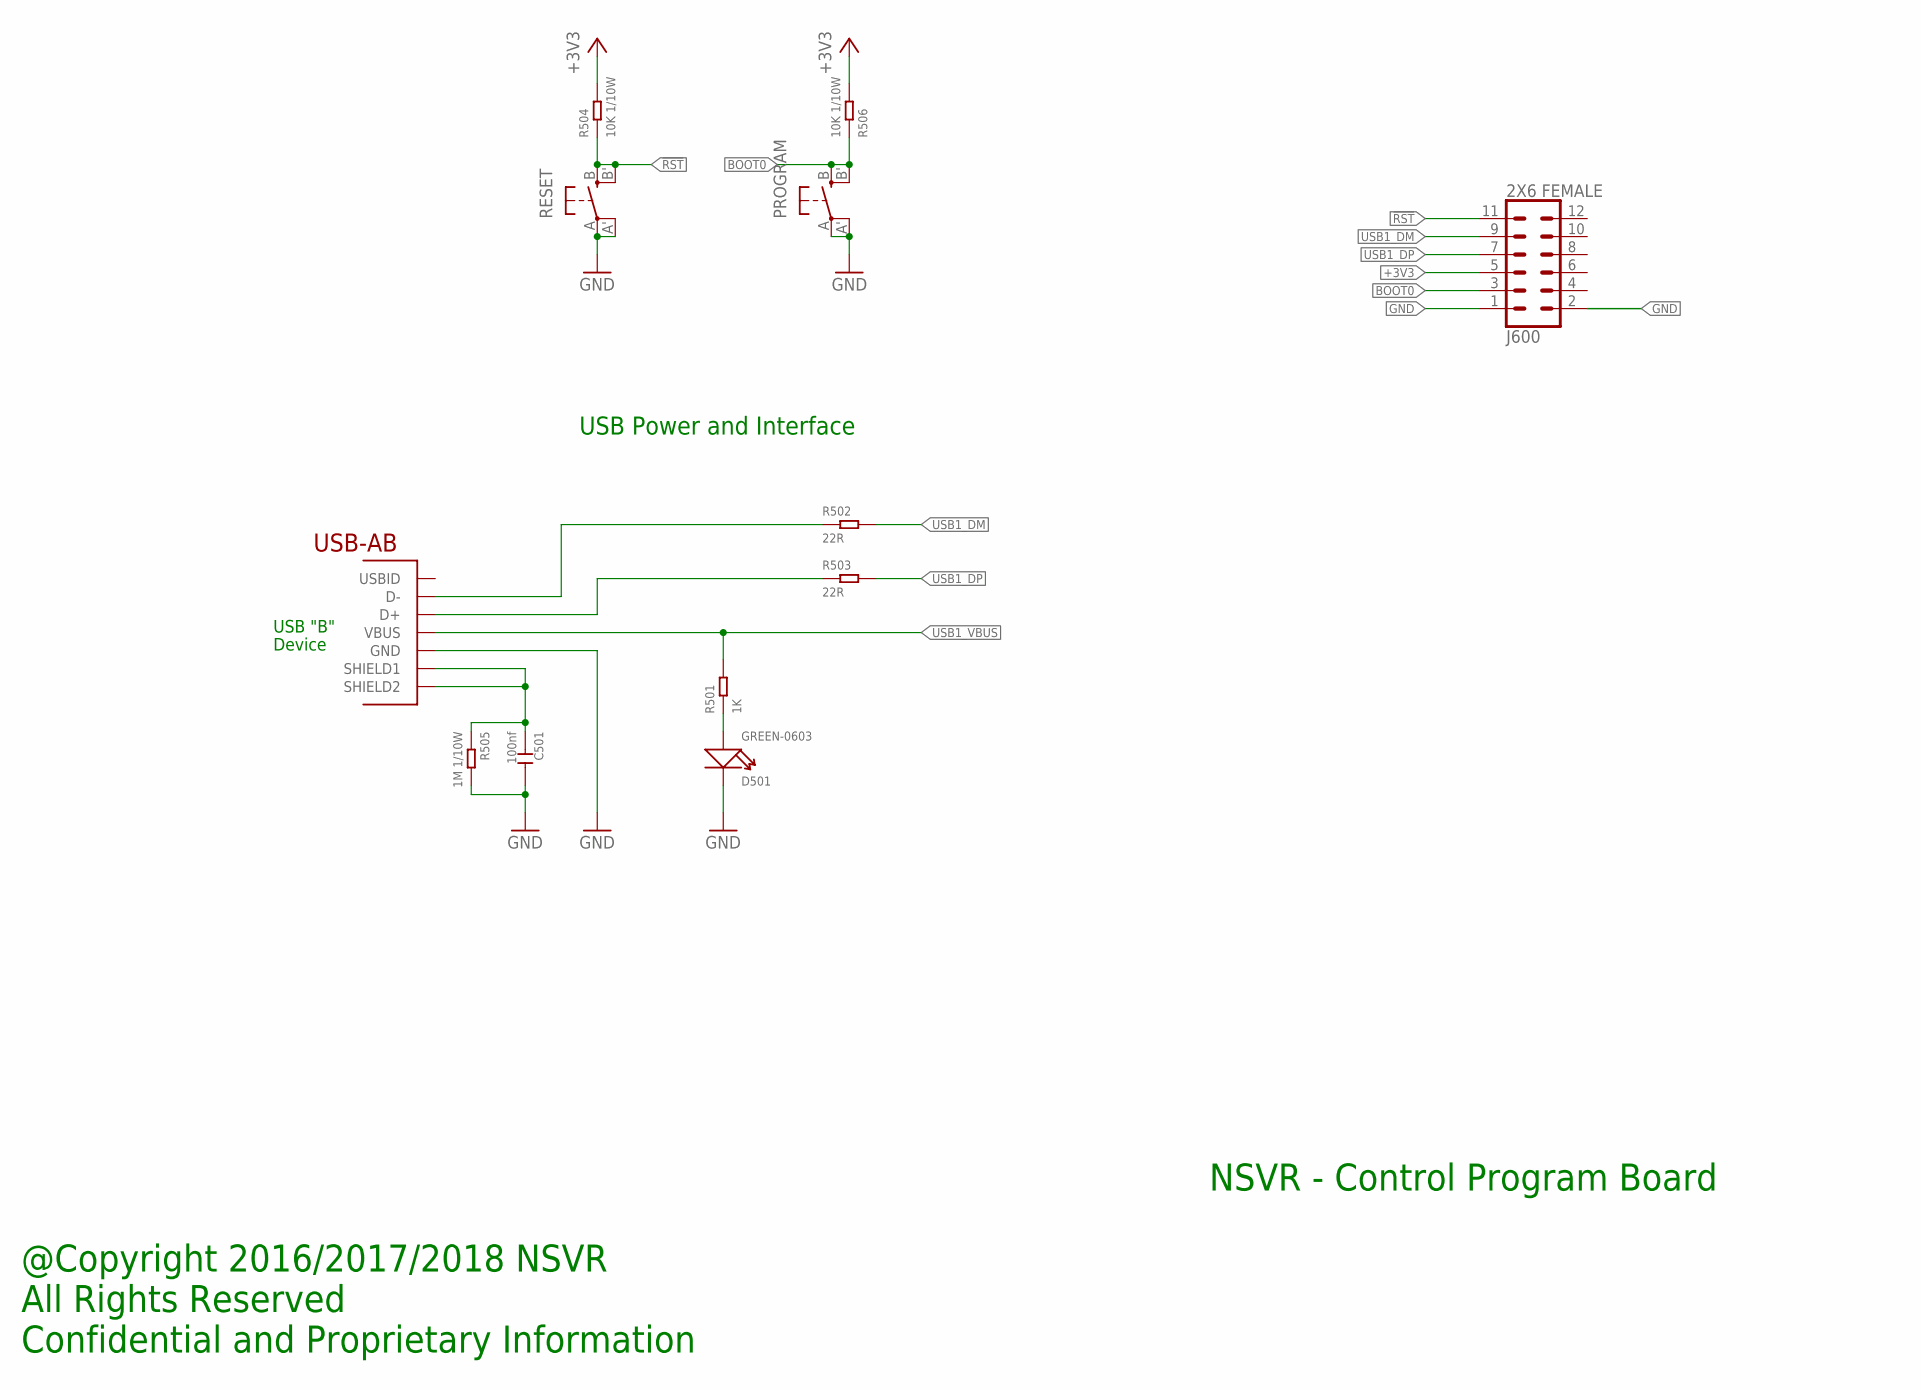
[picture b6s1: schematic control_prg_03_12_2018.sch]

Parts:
C501: 100nf; C0603
D501: GREEN-0603; LED-0603
J600: 2X6 FEMALE; 2X6
PROGRAM: EVQQ2; EVQ-Q2
R501: 1K; R0603
R502, R503: 22R; R0603
R504, R506: 10K 1/10W; R0603
R505: 1M 1/10W; R0603
RESET: EVQQ2; EVQ-Q2
USB501: USB_AB; USB-AB-MICRO-SMD

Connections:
!RST: J600.11, R504.1, RESET.B (S), RESET.B' (S1)
+3V3: J600.5, R504.2, R506.2
BOOT0: J600.3, PROGRAM.B (S), PROGRAM.B' (S1), R506.1
GND: C501.2, D501.-, J600.1, J600.2, PROGRAM.A, PROGRAM.A' (P1), R505.2, RESET.A, RESET.A' (P1), USB501.GND
LED1: D501.+, R501.1
USB1_DM: J600.9, R502.2
USB1_DP: J600.7, R503.2
USB1_M: R502.1, USB501.D-
USB1_P: R503.1, USB501.D+
USB1_SHIELD: C501.1, R505.1, USB501.SHIELD1, USB501.SHIELD2
USB1_VBUS: R501.2, USB501.VBUS

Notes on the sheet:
@Copyright 2016/2017/2018 NSVR All Rights Reserved Confidential and Proprietary Information
NSVR - Control Program Board
USB "B"
Device
USB Power and Interface

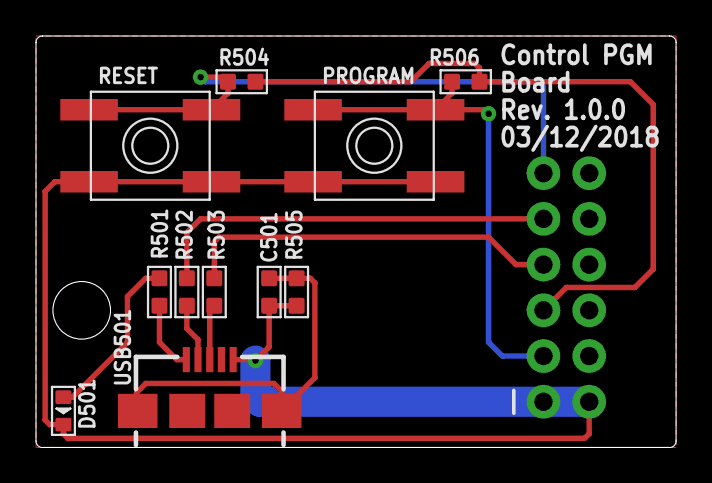
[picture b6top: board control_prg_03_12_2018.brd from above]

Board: 2 copper layers, 35.6 x 22.9 mm, 12 parts (1 on the bottom side), 11 nets.

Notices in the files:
parts and their libraries:
microbuilder: This work is placed in the public domain, and may be freely used for commercial and non-commercial work with the following conditions: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
SparkFun-LED: Licensing: Creative Commons ShareAlike 4.0 International - https://creativecommons.org/licenses/by-sa/4.0
